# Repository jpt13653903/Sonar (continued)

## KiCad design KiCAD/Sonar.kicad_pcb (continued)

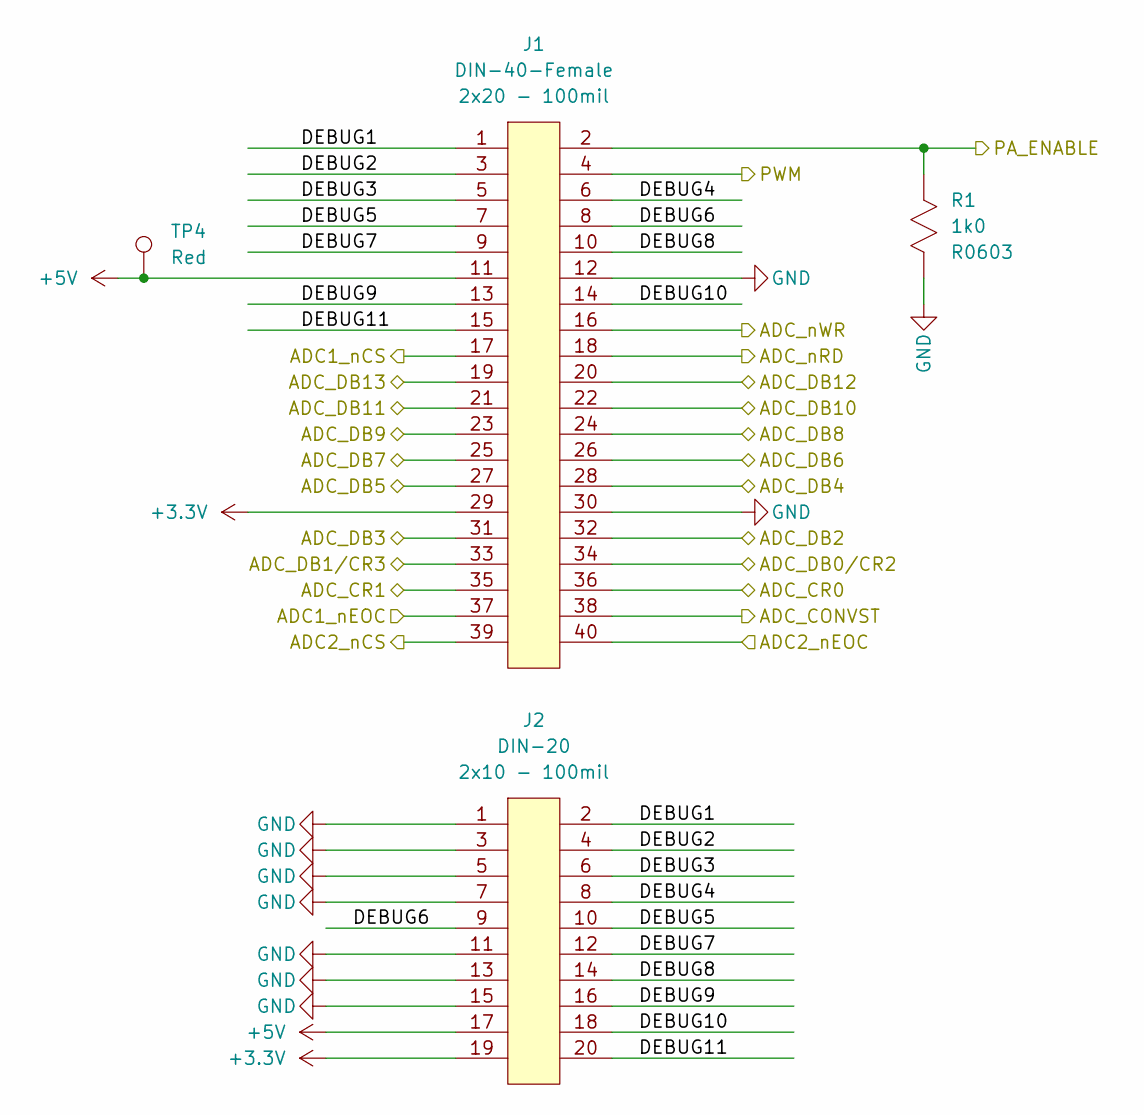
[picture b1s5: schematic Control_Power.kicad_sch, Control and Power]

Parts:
J1: DIN-40-Female; PinSocket_2x20_P2.54mm_Vertical; MPN M20-7832042
J2: DIN-20; IDC-Header_2x10_P2.54mm_Vertical; MPN 70246-2004
R1: R0603_1k0; R_0603_1608Metric; MPN CRGP0603F1K0
TP4: Keystone_5010_Red; TestPoint_Keystone_5010-5014_Multipurpose; MPN 5010

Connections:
+3.3V: J1.29, J2.19; also elsewhere on the board
+5V: J1.11, J2.17, TP4.1 (1_1); also elsewhere on the board
/ADC/CONVST: J1.38; also elsewhere on the board
/ADC/CR0: J1.36; also elsewhere on the board
/ADC/CR1: J1.35; also elsewhere on the board
/ADC/DB0/CR2: J1.34; also elsewhere on the board
/ADC/DB1/CR3: J1.33; also elsewhere on the board
/ADC/DB2: J1.32; also elsewhere on the board
/ADC/DB3: J1.31; also elsewhere on the board
/ADC/DB4: J1.28; also elsewhere on the board
/ADC/DB5: J1.27; also elsewhere on the board
/ADC/DB6: J1.26; also elsewhere on the board
/ADC/DB7: J1.25; also elsewhere on the board
/ADC/DB8: J1.24; also elsewhere on the board
/ADC/DB9: J1.23; also elsewhere on the board
/ADC/DB10: J1.22; also elsewhere on the board
/ADC/DB11: J1.21; also elsewhere on the board
/ADC/DB12: J1.20; also elsewhere on the board
/ADC/DB13: J1.19; also elsewhere on the board
/ADC/nCS1: J1.17; also elsewhere on the board
/ADC/nCS2: J1.39; also elsewhere on the board
/ADC/nEOC1: J1.37; also elsewhere on the board
/ADC/nEOC2: J1.40; also elsewhere on the board
/ADC/nRD: J1.18; also elsewhere on the board
/ADC/nWR: J1.16; also elsewhere on the board
/Control_Power/DEBUG1: J1.1, J2.2
/Control_Power/DEBUG2: J1.3, J2.4
/Control_Power/DEBUG3: J1.5, J2.6
/Control_Power/DEBUG4: J1.6, J2.8
/Control_Power/DEBUG5: J1.7, J2.10
/Control_Power/DEBUG6: J1.8, J2.9
/Control_Power/DEBUG7: J1.9, J2.12
/Control_Power/DEBUG8: J1.10, J2.14
/Control_Power/DEBUG9: J1.13, J2.16
/Control_Power/DEBUG10: J1.14, J2.18
/Control_Power/DEBUG11: J1.15, J2.20
/Control_Power/PA_ENABLE: J1.2, R1.1; also elsewhere on the board
/Control_Power/PWM: J1.4; also elsewhere on the board
GND: J1.12, J1.30, J2.1, J2.3, J2.5, J2.7, J2.11, J2.13, J2.15, R1.2; also elsewhere on the board

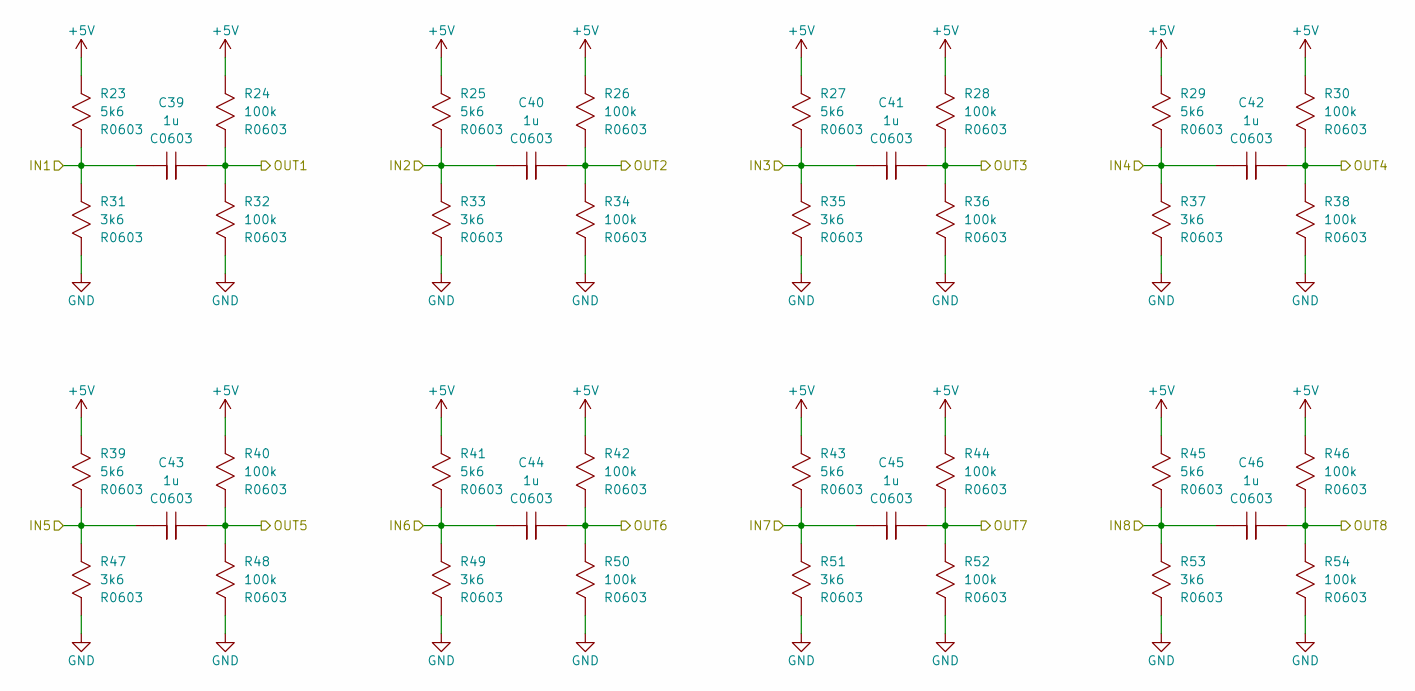
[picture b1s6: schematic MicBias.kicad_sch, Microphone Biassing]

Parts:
C39, C40, C41, C42, C43, C44, C45, C46: C0603_1u0; C_0603_1608Metric; MPN GRT188R61H105KE13D
R23, R25, R27, R29, R39, R41, R43, R45: R0603_5k6; R_0603_1608Metric; MPN CRGP0603F5K6
R24, R26, R28, R30, R32, R34, R36, R38, R40, R42, R44, R46, R48, R50, R52, R54: R0603_100k; R_0603_1608Metric; MPN CRGP0603F100K
R31, R33, R35, R37, R47, R49, R51, R53: R0603_3k6; R_0603_1608Metric; MPN CRGP0603F3K6

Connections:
+5V: R23.1, R24.1, R25.1, R26.1, R27.1, R28.1, R29.1, R30.1, R39.1, R40.1, R41.1, R42.1, R43.1, R44.1, R45.1, R46.1; also elsewhere on the board
/ADC/Amplifier_x8_1/IN1: C39.2, R24.2, R32.1; also elsewhere on the board
/ADC/Amplifier_x8_1/IN2: C40.2, R26.2, R34.1; also elsewhere on the board
/ADC/Amplifier_x8_1/IN3: C41.2, R28.2, R36.1; also elsewhere on the board
/ADC/Amplifier_x8_1/IN4: C42.2, R30.2, R38.1; also elsewhere on the board
/ADC/Amplifier_x8_1/IN5: C43.2, R40.2, R48.1; also elsewhere on the board
/ADC/Amplifier_x8_1/IN6: C44.2, R42.2, R50.1; also elsewhere on the board
/ADC/Amplifier_x8_1/IN7: C45.2, R44.2, R52.1; also elsewhere on the board
/ADC/Amplifier_x8_1/IN8: C46.2, R46.2, R54.1; also elsewhere on the board
/ADC/IN1: C39.1, R23.2, R31.1; also elsewhere on the board
/ADC/IN2: C40.1, R25.2, R33.1; also elsewhere on the board
/ADC/IN3: C41.1, R27.2, R35.1; also elsewhere on the board
/ADC/IN4: C42.1, R29.2, R37.1; also elsewhere on the board
/ADC/IN5: C43.1, R39.2, R47.1; also elsewhere on the board
/ADC/IN6: C44.1, R41.2, R49.1; also elsewhere on the board
/ADC/IN7: C45.1, R43.2, R51.1; also elsewhere on the board
/ADC/IN8: C46.1, R45.2, R53.1; also elsewhere on the board
GND: R31.2, R32.2, R33.2, R34.2, R35.2, R36.2, R37.2, R38.2, R47.2, R48.2, R49.2, R50.2, R51.2, R52.2, R53.2, R54.2; also elsewhere on the board

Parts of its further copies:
C47, C48, C49, C50, C51, C52, C53, C54: C0603_1u0; C_0603_1608Metric; MPN GRT188R61H105KE13D
R55, R57, R59, R61, R71, R73, R75, R77: R0603_5k6; R_0603_1608Metric; MPN CRGP0603F5K6
R56, R58, R60, R62, R64, R66, R68, R70, R72, R74, R76, R78, R80, R82, R84, R86: R0603_100k; R_0603_1608Metric; MPN CRGP0603F100K
R63, R65, R67, R69, R79, R81, R83, R85: R0603_3k6; R_0603_1608Metric; MPN CRGP0603F3K6

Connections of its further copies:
+5V: R55.1, R56.1, R57.1, R58.1, R59.1, R60.1, R61.1, R62.1, R71.1, R72.1, R73.1, R74.1, R75.1, R76.1, R77.1, R78.1; also elsewhere on the board
/ADC/Amplifier_x8_2/IN1: C47.2, R56.2, R64.1; also elsewhere on the board
/ADC/Amplifier_x8_2/IN2: C48.2, R58.2, R66.1; also elsewhere on the board
/ADC/Amplifier_x8_2/IN3: C49.2, R60.2, R68.1; also elsewhere on the board
/ADC/Amplifier_x8_2/IN4: C50.2, R62.2, R70.1; also elsewhere on the board
/ADC/Amplifier_x8_2/IN5: C51.2, R72.2, R80.1; also elsewhere on the board
/ADC/Amplifier_x8_2/IN6: C52.2, R74.2, R82.1; also elsewhere on the board
/ADC/Amplifier_x8_2/IN7: C53.2, R76.2, R84.1; also elsewhere on the board
/ADC/Amplifier_x8_2/IN8: C54.2, R78.2, R86.1; also elsewhere on the board
/ADC/IN9: C47.1, R55.2, R63.1; also elsewhere on the board
/ADC/IN10: C48.1, R57.2, R65.1; also elsewhere on the board
/ADC/IN11: C49.1, R59.2, R67.1; also elsewhere on the board
/ADC/IN12: C50.1, R61.2, R69.1; also elsewhere on the board
/ADC/IN13: C51.1, R71.2, R79.1; also elsewhere on the board
/ADC/IN14: C52.1, R73.2, R81.1; also elsewhere on the board
/ADC/IN15: C53.1, R75.2, R83.1; also elsewhere on the board
/ADC/IN16: C54.1, R77.2, R85.1; also elsewhere on the board
GND: R63.2, R64.2, R65.2, R66.2, R67.2, R68.2, R69.2, R70.2, R79.2, R80.2, R81.2, R82.2, R83.2, R84.2, R85.2, R86.2; also elsewhere on the board

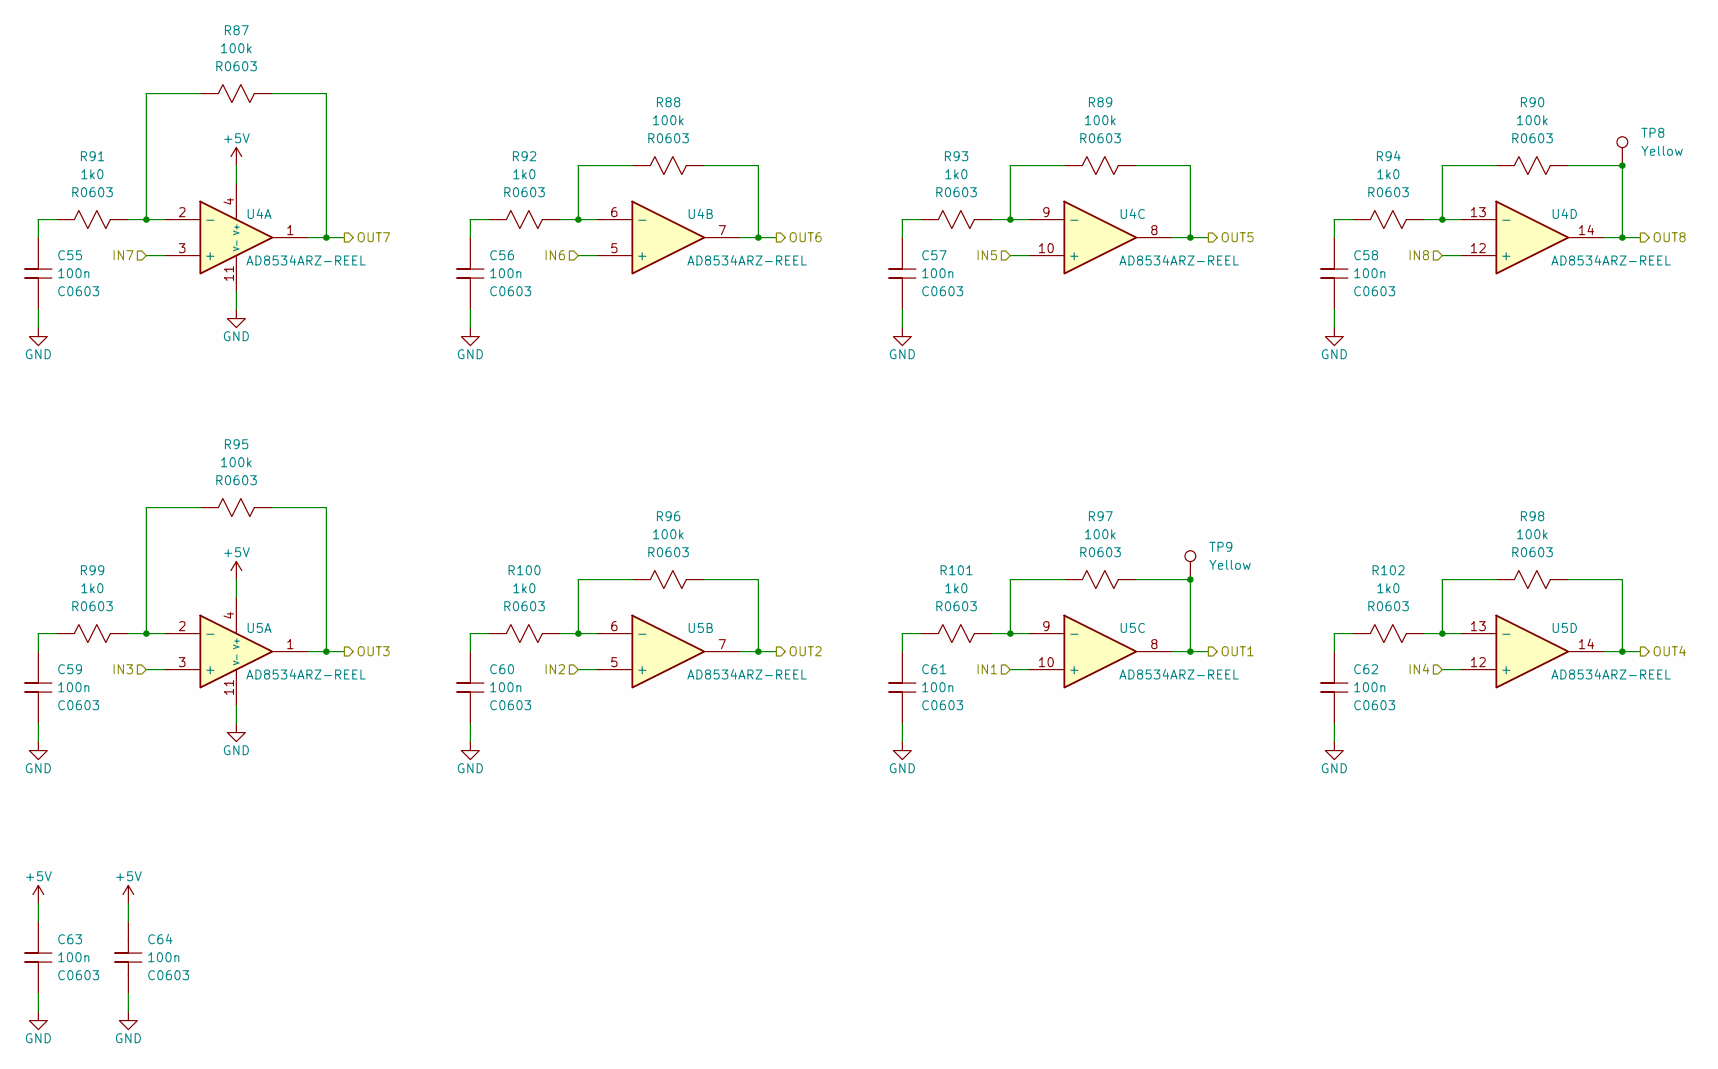
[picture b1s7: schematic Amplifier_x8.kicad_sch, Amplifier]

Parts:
C55, C56, C57, C58, C59, C60, C61, C62, C63, C64: C0603_100n; C_0603_1608Metric; MPN 06035C104KAT2A
R87, R88, R89, R90, R95, R96, R97, R98: R0603_100k; R_0603_1608Metric; MPN CRGP0603F100K
R91, R92, R93, R94, R99, R100, R101, R102: R0603_1k0; R_0603_1608Metric; MPN CRGP0603F1K0
TP8, TP9: Keystone_5014_Yellow; TestPoint_Keystone_5010-5014_Multipurpose; MPN 5014
U4, U5: AD8534ARZ-REEL; SOIC127P600X175-14N; MPN AD8534ARZ-REEL

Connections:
+5V: C63.1, C64.1, U4.4 (V+), U5.4 (V+); also elsewhere on the board
/ADC/Amplifier_x8_1/IN1: U5.10 (+); also elsewhere on the board
/ADC/Amplifier_x8_1/IN2: U5.5 (+); also elsewhere on the board
/ADC/Amplifier_x8_1/IN3: U5.3 (+); also elsewhere on the board
/ADC/Amplifier_x8_1/IN4: U5.12 (+); also elsewhere on the board
/ADC/Amplifier_x8_1/IN5: U4.10 (+); also elsewhere on the board
/ADC/Amplifier_x8_1/IN6: U4.5 (+); also elsewhere on the board
/ADC/Amplifier_x8_1/IN7: U4.3 (+); also elsewhere on the board
/ADC/Amplifier_x8_1/IN8: U4.12 (+); also elsewhere on the board
/ADC/Amplifier_x8_1/OUT1: R97.2, TP9.1 (1_1), U5.8; also elsewhere on the board
/ADC/Amplifier_x8_1/OUT2: R96.2, U5.7; also elsewhere on the board
/ADC/Amplifier_x8_1/OUT3: R95.2, U5.1; also elsewhere on the board
/ADC/Amplifier_x8_1/OUT4: R98.2, U5.14; also elsewhere on the board
/ADC/Amplifier_x8_1/OUT5: R89.2, U4.8; also elsewhere on the board
/ADC/Amplifier_x8_1/OUT6: R88.2, U4.7; also elsewhere on the board
/ADC/Amplifier_x8_1/OUT7: R87.2, U4.1; also elsewhere on the board
/ADC/Amplifier_x8_1/OUT8: R90.2, TP8.1 (1_1), U4.14; also elsewhere on the board
GND: C55.2, C56.2, C57.2, C58.2, C59.2, C60.2, C61.2, C62.2, C63.2, C64.2, U4.11 (V-), U5.11 (V-); also elsewhere on the board
unnamed: C55.1, R91.1
unnamed: C56.1, R92.1
unnamed: C57.1, R93.1
unnamed: C58.1, R94.1
unnamed: C59.1, R99.1
unnamed: C60.1, R100.1
unnamed: C61.1, R101.1
unnamed: C62.1, R102.1
unnamed: R87.1, R91.2, U4.2 (-)
unnamed: R88.1, R92.2, U4.6 (-)
unnamed: R89.1, R93.2, U4.9 (-)
unnamed: R90.1, R94.2, U4.13 (-)
unnamed: R95.1, R99.2, U5.2 (-)
unnamed: R96.1, R100.2, U5.6 (-)
unnamed: R97.1, R101.2, U5.9 (-)
unnamed: R98.1, R102.2, U5.13 (-)

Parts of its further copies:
C65, C66, C67, C68, C69, C70, C71, C72, C73, C74: C0603_100n; C_0603_1608Metric; MPN 06035C104KAT2A
R103, R104, R105, R106, R111, R112, R113, R114: R0603_100k; R_0603_1608Metric; MPN CRGP0603F100K
R107, R108, R109, R110, R115, R116, R117, R118: R0603_1k0; R_0603_1608Metric; MPN CRGP0603F1K0
TP10, TP11: Keystone_5014_Yellow; TestPoint_Keystone_5010-5014_Multipurpose; MPN 5014
U6, U7: AD8534ARZ-REEL; SOIC127P600X175-14N; MPN AD8534ARZ-REEL

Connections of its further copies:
+5V: C73.1, C74.1, U6.4 (V+), U7.4 (V+); also elsewhere on the board
/ADC/Amplifier_x8_2/IN1: U7.10 (+); also elsewhere on the board
/ADC/Amplifier_x8_2/IN2: U7.5 (+); also elsewhere on the board
/ADC/Amplifier_x8_2/IN3: U7.3 (+); also elsewhere on the board
/ADC/Amplifier_x8_2/IN4: U7.12 (+); also elsewhere on the board
/ADC/Amplifier_x8_2/IN5: U6.10 (+); also elsewhere on the board
/ADC/Amplifier_x8_2/IN6: U6.5 (+); also elsewhere on the board
/ADC/Amplifier_x8_2/IN7: U6.3 (+); also elsewhere on the board
/ADC/Amplifier_x8_2/IN8: U6.12 (+); also elsewhere on the board
/ADC/Amplifier_x8_2/OUT1: R113.2, TP11.1 (1_1), U7.8; also elsewhere on the board
/ADC/Amplifier_x8_2/OUT2: R112.2, U7.7; also elsewhere on the board
/ADC/Amplifier_x8_2/OUT3: R111.2, U7.1; also elsewhere on the board
/ADC/Amplifier_x8_2/OUT4: R114.2, U7.14; also elsewhere on the board
/ADC/Amplifier_x8_2/OUT5: R105.2, U6.8; also elsewhere on the board
/ADC/Amplifier_x8_2/OUT6: R104.2, U6.7; also elsewhere on the board
/ADC/Amplifier_x8_2/OUT7: R103.2, U6.1; also elsewhere on the board
/ADC/Amplifier_x8_2/OUT8: R106.2, TP10.1 (1_1), U6.14; also elsewhere on the board
GND: C65.2, C66.2, C67.2, C68.2, C69.2, C70.2, C71.2, C72.2, C73.2, C74.2, U6.11 (V-), U7.11 (V-); also elsewhere on the board
unnamed: C65.1, R107.1
unnamed: C66.1, R108.1
unnamed: C67.1, R109.1
unnamed: C68.1, R110.1
unnamed: C69.1, R115.1
unnamed: C70.1, R116.1
unnamed: C71.1, R117.1
unnamed: C72.1, R118.1
unnamed: R103.1, R107.2, U6.2 (-)
unnamed: R104.1, R108.2, U6.6 (-)
unnamed: R105.1, R109.2, U6.9 (-)
unnamed: R106.1, R110.2, U6.13 (-)
unnamed: R111.1, R115.2, U7.2 (-)
unnamed: R112.1, R116.2, U7.6 (-)
unnamed: R113.1, R117.2, U7.9 (-)
unnamed: R114.1, R118.2, U7.13 (-)

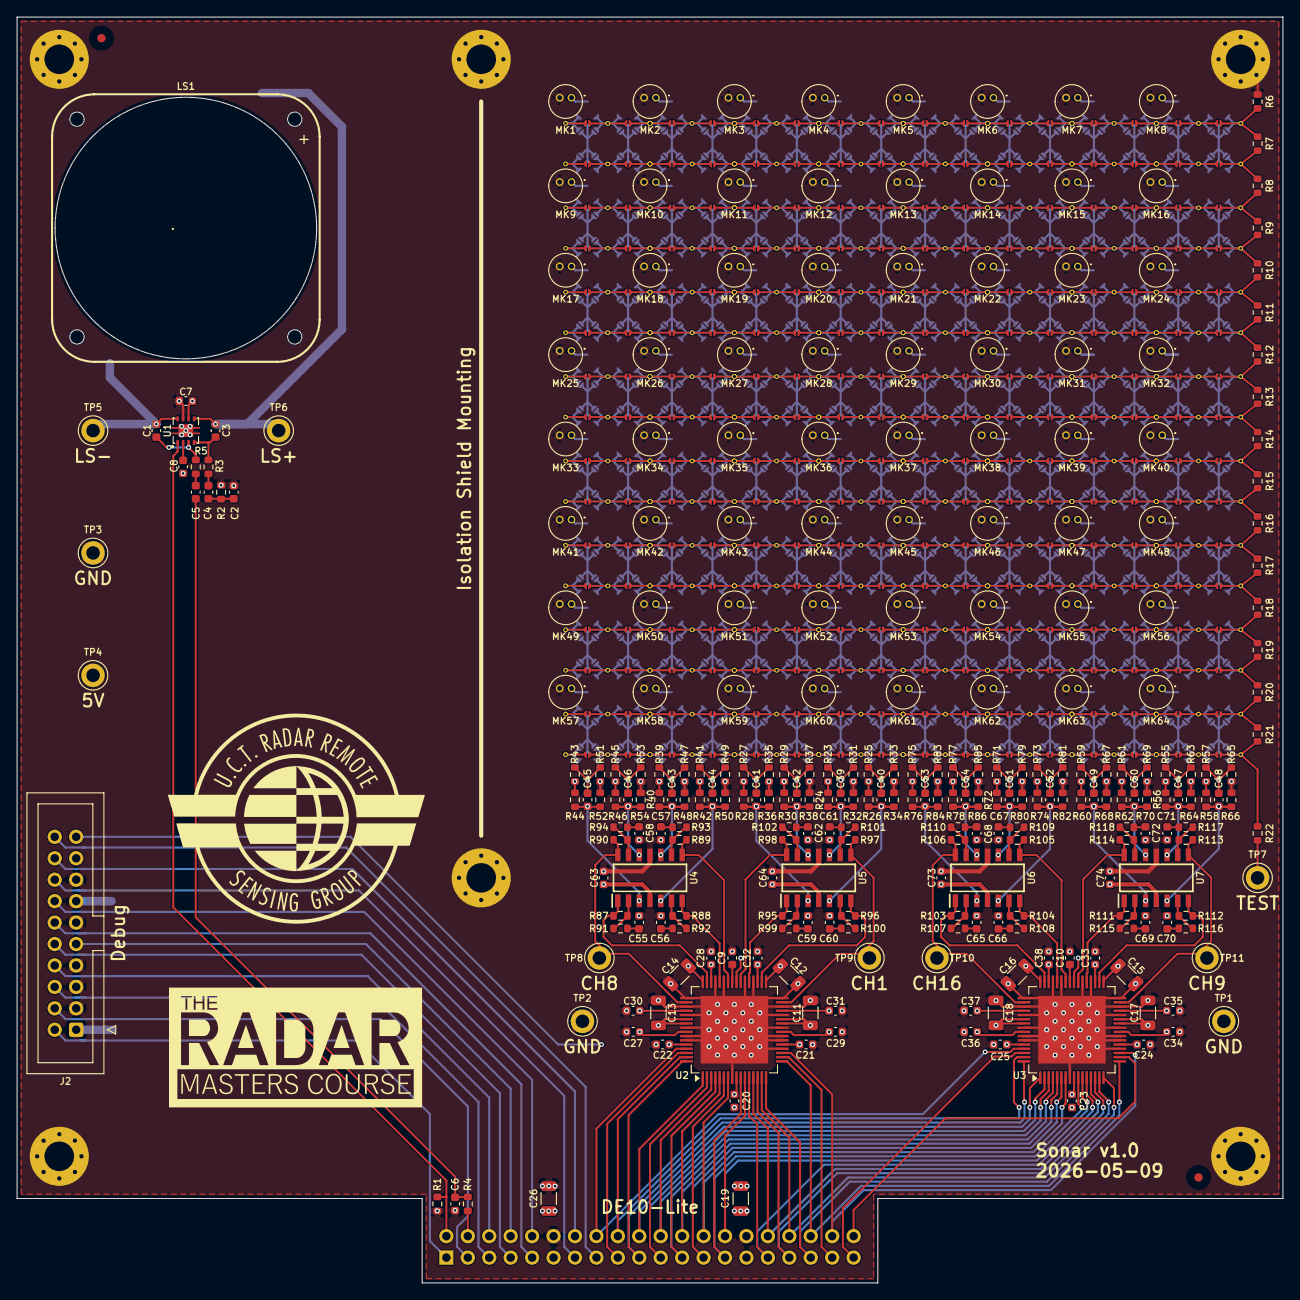
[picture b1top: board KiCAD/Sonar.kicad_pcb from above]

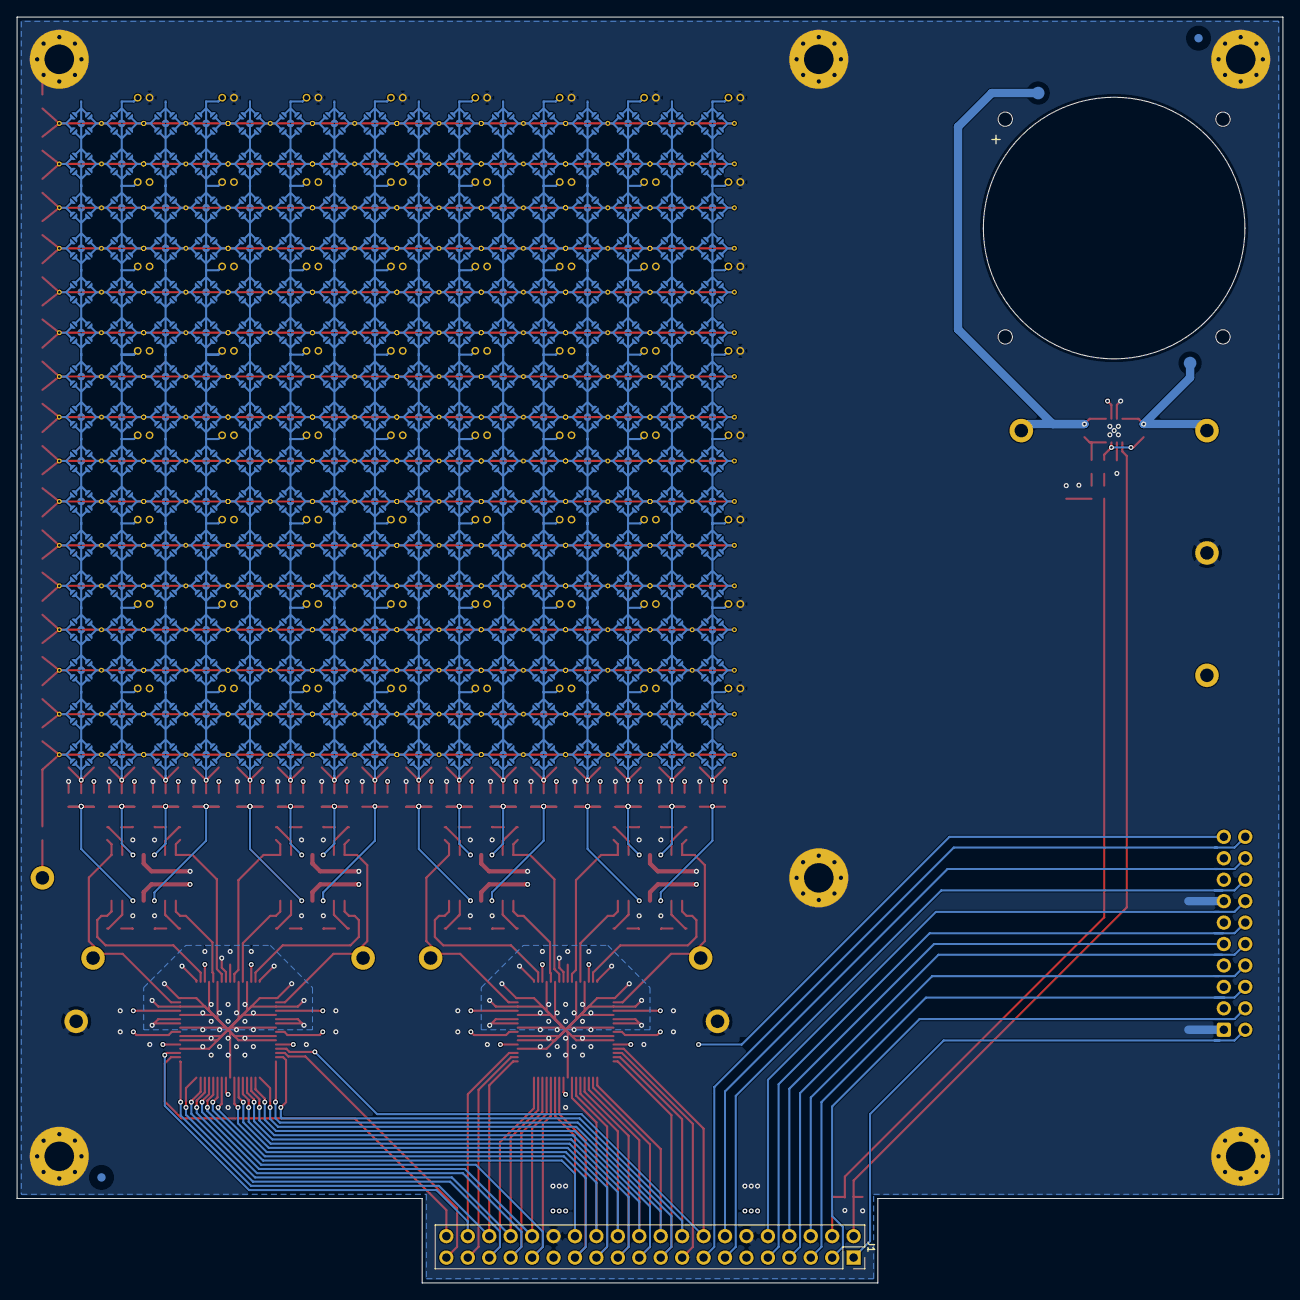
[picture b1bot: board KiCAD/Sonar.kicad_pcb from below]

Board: 4 copper layers, 150.0 x 150.0 mm, 353 parts (3 on the bottom side), 381 nets.

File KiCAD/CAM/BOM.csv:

"Reference","Qty","Value","MPN","Manufacturer"
"C1,C3","2","C0603_100p","KGM15AR71H101K","KYOCERA AVX"
"C2,C6","2","C0603_2n2","GRM1885C1H222JA01D","Murata"
"C4,C5,C8","3","C0603_220n","GCM188R71E224MA55J","Murata"
"C7,C39,C40,C41,C42,C43,C44,C45,C46,C47,C48,C49,C50,C51,C52,C53,C54","17","C0603_1u0","GRT188R61H105KE13D","MuRata"
"C9,C10,C20,C21,C22,C23,C24,C25,C27,C28,C29,C30,C31,C32,C33,C34,C35,C36,C37,C38,C55,C56,C57,C58,C59,C60,C61,C62,C63,C64,C65,C66,C67,C68,C69,C70,C71,C72,C73,C74","40","C0603_100n","06035C104KAT2A","KYOCERA AVX"
"C11,C12,C13,C14,C15,C16,C17,C18,C19,C26","10","C1206_22u","C1206C226M4PACTU","Kemet"
"J1","1","DIN-40-Female","M20-7832042","Harwin"
"J2","1","DIN-20","70246-2004","Molex"
"R1,R2,R4,R91,R92,R93,R94,R99,R100,R101,R102,R107,R108,R109,R110,R115,R116,R117,R118","19","R0603_1k0","CRGP0603F1K0","TE Connectivity"
"R3,R5","2","R0603_12k","CRGP0603F12K","TE Connectivity"
"R6,R7,R8,R9,R10,R11,R12,R13,R14,R15,R16,R17,R18,R19,R20,R21","16","R0603_10R","CRGP0603F10R","TE Connectivity"
"R22,R31,R33,R35,R37,R47,R49,R51,R53,R63,R65,R67,R69,R79,R81,R83,R85","17","R0603_3k6","CRGP0603F3K6","TE Connectivity"
"R23,R25,R27,R29,R39,R41,R43,R45,R55,R57,R59,R61,R71,R73,R75,R77","16","R0603_5k6","CRGP0603F5K6","TE Connectivity"
"R24,R26,R28,R30,R32,R34,R36,R38,R40,R42,R44,R46,R48,R50,R52,R54,R56,R58,R60,R62,R64,R66,R68,R70,R72,R74,R76,R78,R80,R82,R84,R86,R87,R88,R89,R90,R95,R96,R97,R98,R103,R104,R105,R106,R111,R112,R113,R114","48","R0603_100k","CRGP0603F100K","TE Connectivity"
"TP1,TP2,TP3","3","Keystone_5011_Black","5011","Keystone"
"TP4","1","Keystone_5010_Red","5010","Keystone"
"TP5,TP6,TP7,TP8,TP9,TP10,TP11","7","Keystone_5014_Yellow","5014","Keystone"
"U1","1","TPA6211A1DRBR","TPA6211A1DRBR","Texas Instruments"
"U2,U3","2","MAX11059","MAX11059ECB+","Analog Devices"
"U4,U5,U6,U7","4","AD8534ARZ-REEL","AD8534ARZ-REEL","Analog Devices"

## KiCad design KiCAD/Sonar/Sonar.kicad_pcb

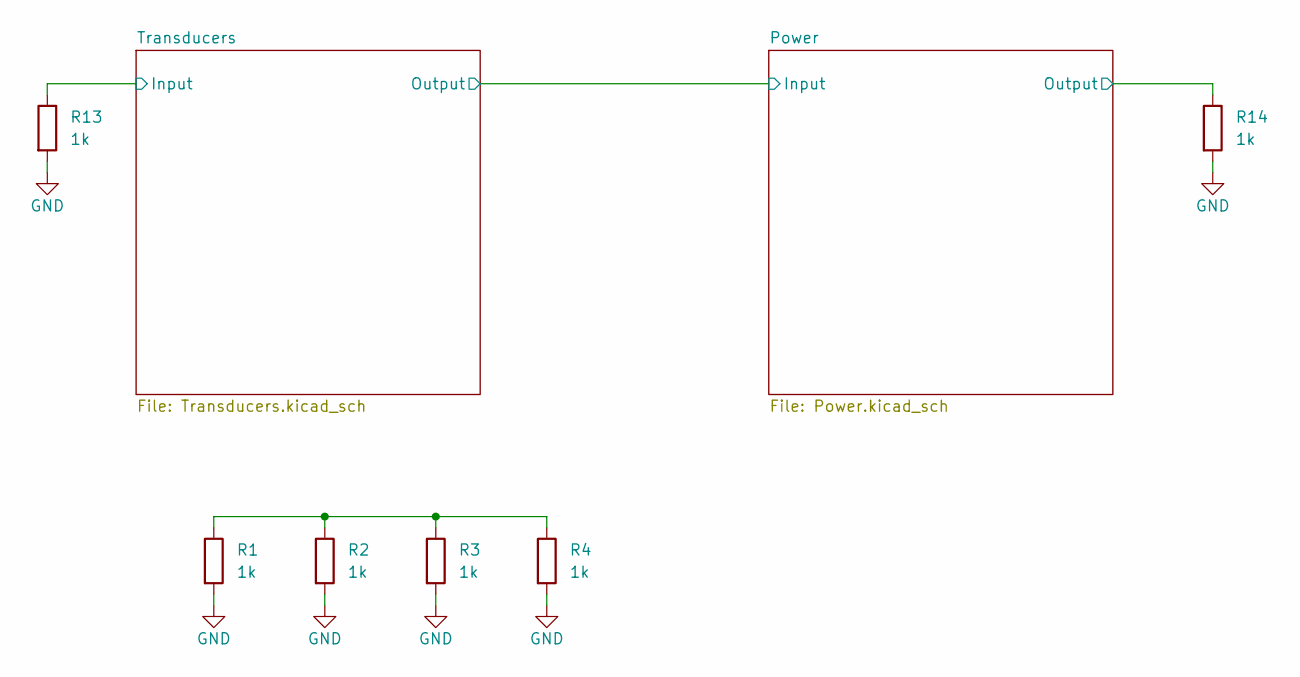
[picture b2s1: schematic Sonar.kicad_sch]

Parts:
R1, R2, R3, R4, R13, R14: 1k; R_0603_1608Metric

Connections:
/Power/Output: R14.1; also elsewhere on the board
/Transducers/Input: R13.1; also elsewhere on the board
GND: R1.2, R2.2, R3.2, R4.2, R13.2, R14.2; also elsewhere on the board
unnamed: R1.1, R2.1, R3.1, R4.1

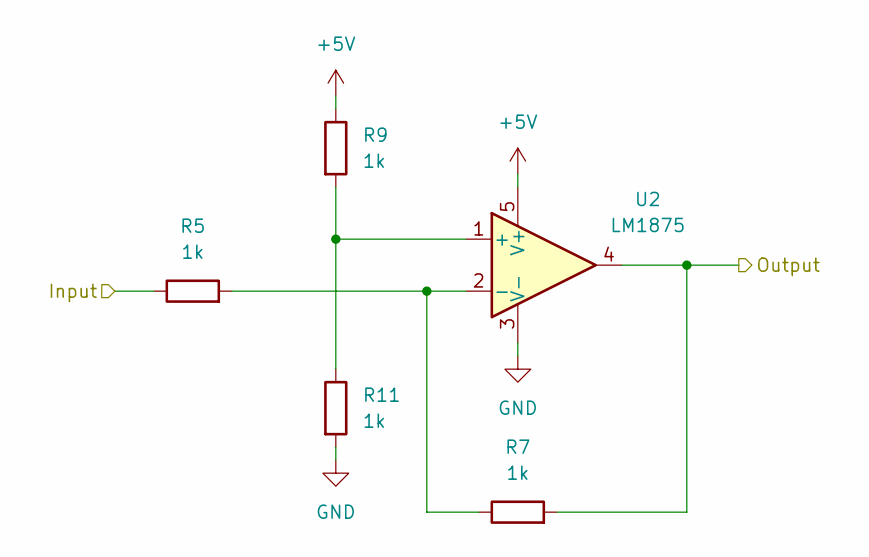
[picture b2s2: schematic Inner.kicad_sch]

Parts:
R5, R7, R9, R11: 1k; R_0603_1608Metric
U2: LM1875; TO-220-5_P3.4x3.7mm_StaggerOdd_Lead3.8mm_Vertical

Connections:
+5V: R9.1, U2.5 (V+); also elsewhere on the board
/Power/Input: R5.1; also elsewhere on the board
/Power/Output: R7.2, U2.4; also elsewhere on the board
GND: R11.2, U2.3 (V-); also elsewhere on the board
unnamed: R9.2, R11.1, U2.1 (+)
unnamed: R5.2, R7.1, U2.2 (-)

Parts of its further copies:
R6, R8, R10, R12: 1k; R_0603_1608Metric
U3: LM1875; TO-220-5_P3.4x3.7mm_StaggerOdd_Lead3.8mm_Vertical

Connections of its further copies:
+5V: R8.1, U3.5 (V+); also elsewhere on the board
/Power/Input: R12.2, U3.4; also elsewhere on the board
/Transducers/Input: R6.1; also elsewhere on the board
GND: R10.2, U3.3 (V-); also elsewhere on the board
unnamed: R8.2, R10.1, U3.1 (+)
unnamed: R6.2, R12.1, U3.2 (-)

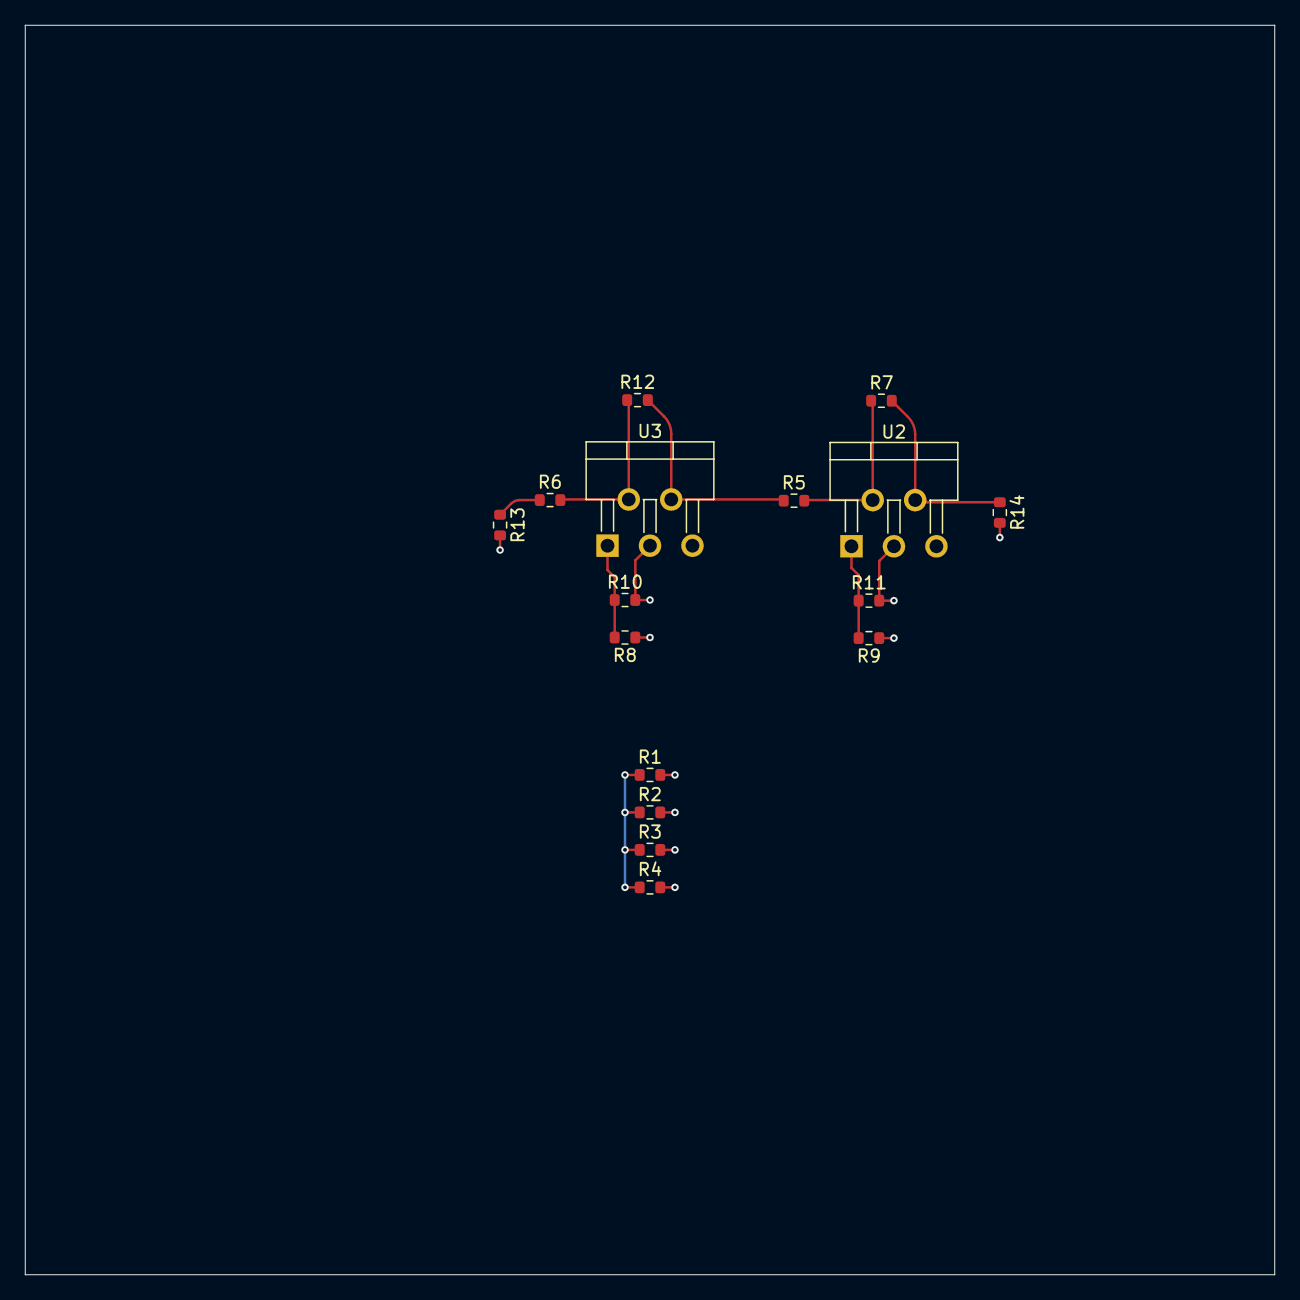
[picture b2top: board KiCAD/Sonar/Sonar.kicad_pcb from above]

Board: 4 copper layers, 100.0 x 100.0 mm, 16 parts (0 on the bottom side), 10 nets.

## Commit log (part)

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2026-05-07 Added CERN-OHL-P licence
2026-05-07 Preliminary block diagram with parts selection
2026-05-07 Added some parts details
2026-05-07 Added an SVG with Rx pattern options
2026-05-07 Toy KiCAD project to get a feel for the tool
2026-05-07 Completed the schematic
2026-05-08 Drew the footprint for the cross-bar switch
2026-05-08 Finished routing
2026-05-08 Added RRSG and RadarMasters logos
2026-05-08 Added a debug header
2026-05-08 Cosmetics and fiducials
2026-05-08 Added test-points
2026-05-08 Added the block diagram to the readme
2026-05-08 Organisd the assembly layer
2026-05-08 Added .history_trim to the .gitignore
2026-05-08 Set up and exported the BOM
2026-05-08 Set up and exported the CAM files
2026-05-09 Added PA_Enable pull-down and moved the debug header
2026-05-09 Moved the microphone RL to per-channel instead of per-mic
2026-05-09 Added title block and version text
2026-05-09 Regenerated CAM output
2026-05-09 Updated the block diagram to match the latest design
2026-05-09 Final Updates:
    - Mounting holes for an isolation shield
    - 5V test-point to inject power
    - Test signal input with resistor ladder
2026-05-10 Updated speaker and microphone library path to "Transducers"
2026-05-10 Updated KiCAD/.gitignore to exclude zip files
2026-05-10 Added 3D renders
2026-05-10 Added 3D renders and a better description to the readme
2026-05-10 Fixed the block diagram grid origin
2026-05-11 BOM EQ
2026-05-11 Accepted the BOM updates
2026-06-06 Changed 100pF and 100nF to AVX parts, and gave TPA6211 a pin-1 dot
2026-06-06 Regenerated the datapack
